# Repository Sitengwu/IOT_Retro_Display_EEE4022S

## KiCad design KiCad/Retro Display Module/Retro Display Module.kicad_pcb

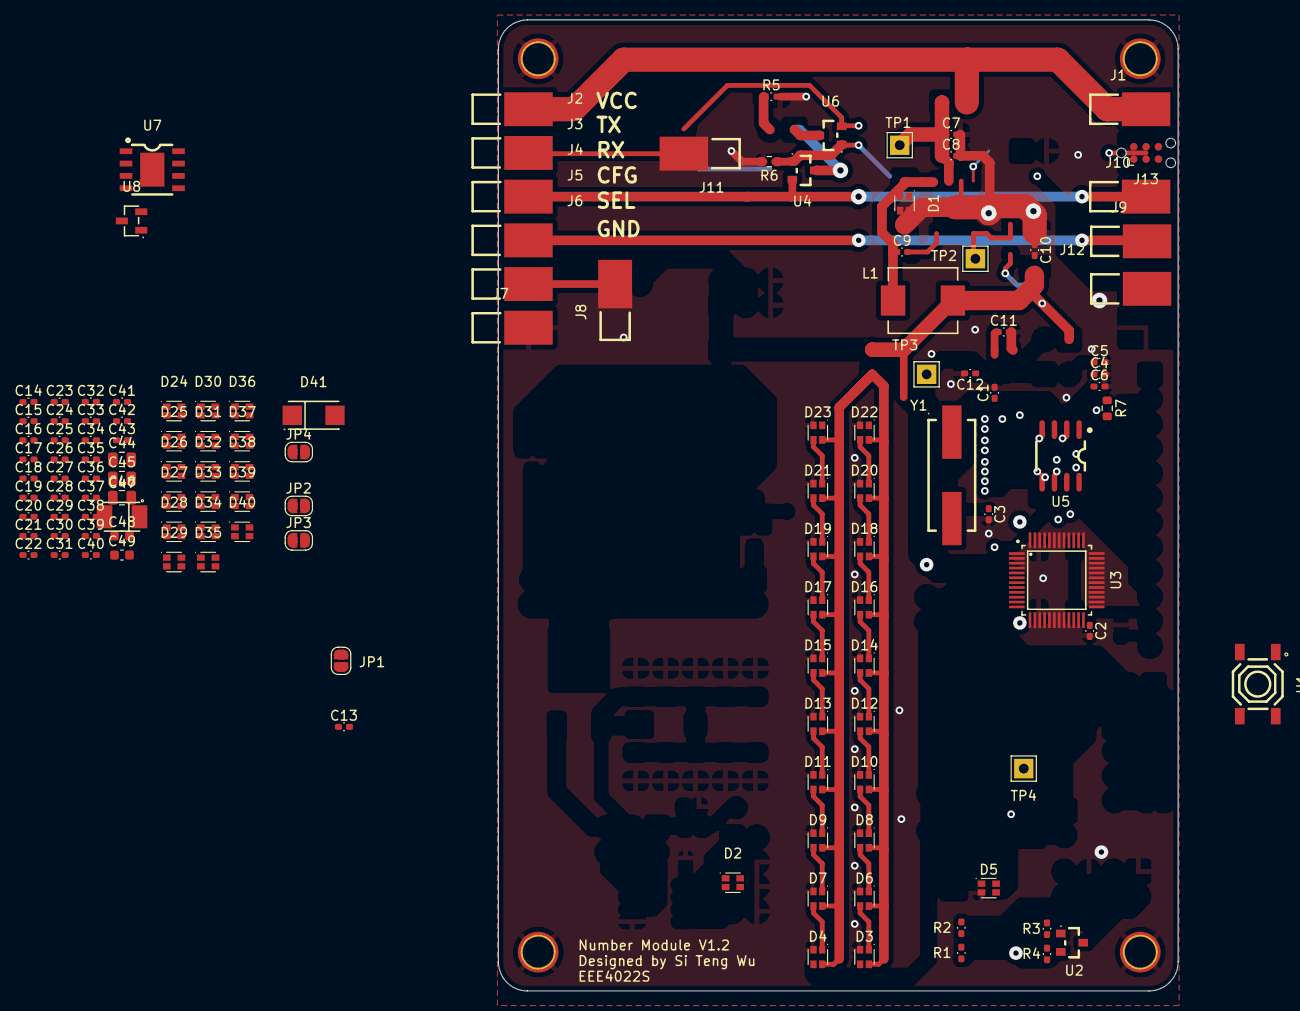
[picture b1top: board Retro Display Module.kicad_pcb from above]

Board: 2 copper layers, 70.0 x 100.0 mm, 132 parts (0 on the bottom side), 64 nets.

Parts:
C1, C3: 10pF; C_0402_1005Metric_Pad0.74x0.62mm_HandSolder
C2, C4, C5, C7, C8, C9, C10, C11, C12, C13, C14, C15, C16, C17, C18, C19, C20, C21, C22, C23, C24, C25, C26, C27, C28, C29, C30, C31, C32, C33, C34, C35, C36, C37, C38, C39, C40, C41, C42, C43: 0.1uF; C_0402_1005Metric_Pad0.74x0.62mm_HandSolder
C6: 4.7uF; C_0402_1005Metric_Pad0.74x0.62mm_HandSolder
C44, C45: 4.7uF; C_0805_2012Metric
C46: 10nF; C_0805_2012Metric
C47: 220uF; CAP-SMD_L3.5-W2.8
C48, C49: 1uF; C_0603_1608Metric
D1, D2, D3, D4, D5, D6, D7, D8, D9, D10, D11, D12, D13, D14, D15, D16, D17, D18, D19, D20, D21, D22, D23, D24, D25, D26, D27, D28, D29, D30, D31, D32, D33, D34, D35, D36, D37, D38, D39, D40: XL-1615RGBC-WS2812B; LED-SMD_4P-L1.6-W1.5_XL-1615RGBC-WS2812B
D41: SS34; SMA_L4.3-W2.6-LS5.2-RD
H1, H2, H3, H4: M3; MountingHole_3.2mm_M3_Pad_TopBottom
J1, J7: VCC; CONN-SMD_YZF0002-38080-02
J2, J8: TX; CONN-SMD_YZF0002-38080-02
J3, J9: RX; CONN-SMD_YZF0002-38080-02
J4, J10: CFG; CONN-SMD_YZF0002-38080-02
J5, J11: SEL; CONN-SMD_YZF0002-38080-02
J6, J12: GND; CONN-SMD_YZF0002-38080-02
J13: Conn_02x03_Odd_Even; Tag-Connect_TC2030-IDC-NL_2x03_P1.27mm_Vertical
JP1, JP2, JP3, JP4: Jumper_2_Open; SolderJumper-2_P1.3mm_Open_RoundedPad1.0x1.5mm
L1: 22uH; IND-SMD_L7.3-W6.6_MHCI06030
R1: 100k; R_0402_1005Metric_Pad0.72x0.64mm_HandSolder
R2, R3, R5: 1k; R_0402_1005Metric_Pad0.72x0.64mm_HandSolder
R4: 10k; R_0402_1005Metric_Pad0.72x0.64mm_HandSolder
R6: 12k; R_0603_1608Metric
R7: 3.9k; R_0603_1608Metric
TP1, TP2, TP3, TP4: TestPoint; TestPoint_THTPad_2.0x2.0mm_Drill1.0mm
U1: TS-1187A-B-A-B; SW-SMD_4P-L5.1-W5.1-P3.70-LS6.5-TL-2
U2, U4, U6: AO3401A; SOT-23_L2.9-W1.3-P1.90-LS2.4-BR
U3: STM32G030C8T6; LQFP-48_L7.0-W7.0-P0.50-LS9.0-BL_1
U5: LM358; Dual LM358
U7: TPS5430DDAR; ESOP-8_L4.9-W3.9-P1.27-LS6.0-TL-EP
U8: XC6206P332MR; SOT-23-3_L2.9-W1.3-P1.90-LS2.4-BR
Y1: Crystal; CRYSTAL-SMD_L11.5-W4.8-LS12.7

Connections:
/3V3: C4.1, C6.1, C7.1, J5.1, J13.1, JP2.1 (A), U3.4 (VBAT), U3.5 (VREF+), U3.6 (VDDA/DDA)
/5V: C8.1, C9.1, C10.1, C11.1, C12.1, C13.1, C14.1, C15.1, C16.1, C17.1, C18.1, C19.1, C20.1, C21.1, C22.1, C23.1, C24.1, C25.1, C26.1, C27.1, C28.1, C29.1, C30.1, C31.1, C32.1, C33.1, C34.1, C35.1, C36.1, C37.1, C38.1, C39.1, C40.1, C41.1, C42.1, C43.1, D1.2 (VDD), D2.2 (VDD), D3.2 (VDD), D4.2 (VDD), D5.2 (VDD), D6.2 (VDD), D7.2 (VDD), D8.2 (VDD), D9.2 (VDD), D10.2 (VDD), D11.2 (VDD), D12.2 (VDD), D13.2 (VDD), D14.2 (VDD), D15.2 (VDD), D16.2 (VDD), D17.2 (VDD), D18.2 (VDD), D19.2 (VDD), D20.2 (VDD), D21.2 (VDD), D22.2 (VDD), D23.2 (VDD), D24.2 (VDD), D25.2 (VDD), D26.2 (VDD), D27.2 (VDD), D28.2 (VDD), D29.2 (VDD), D30.2 (VDD), D31.2 (VDD), D32.2 (VDD), D33.2 (VDD), D34.2 (VDD), D35.2 (VDD), D36.2 (VDD), D37.2 (VDD), D38.2 (VDD), D39.2 (VDD), D40.2 (VDD), JP1.1 (A)
/NRST: C2.1, J13.3, U1.1 (A), U1.2 (B), U3.10 (NRST)
/PA1: J4.1, J10.1, R5.1
/Power/3V3: C49.1, JP2.2 (B), TP4.1, U8.2 (Vout)
/Power/5V: C47.1, C48.1, JP1.2 (B), L1.2, R6.1, TP3.1, U8.3 (Vin)
/Power/VCC: JP3.2 (B), U5.2 (-), U6.3 (D)
/SWDCLK/BOOT: J13.4, R4.2, U3.36 (PA14-BOOT0)
/SWDIO: J13.2, U3.35 (PA13)
/TIM1_CH1: D1.4 (DI), D2.4 (DI), D3.4 (DI), D4.4 (DI), U3.28 (PA8)
/USART2_Rx: J2.1, R2.1
/USART2_Tx: J8.1, R3.1, U4.2 (S)
/VCC: J1.1, J7.1, JP3.1 (A)
GND: C1.2, C2.2, C3.2, C4.2, C5.2, C6.2, C7.2, C8.2, C9.2, C10.2, C11.2, C12.2, C13.2, C14.2, C15.2, C16.2, C17.2, C18.2, C19.2, C20.2, C21.2, C22.2, C23.2, C24.2, C25.2, C26.2, C27.2, C28.2, C29.2, C30.2, C31.2, C32.2, C33.2, C34.2, C35.2, C36.2, C37.2, C38.2, C39.2, C40.2, C41.2, C42.2, C43.2, C44.2, C45.2, C47.2, C48.2, C49.2, D1.3 (GND), D2.3 (GND), D3.3 (GND), D4.3 (GND), D5.3 (GND), D6.3 (GND), D7.3 (GND), D8.3 (GND), D9.3 (GND), D10.3 (GND), D11.3 (GND), D12.3 (GND), D13.3 (GND), D14.3 (GND), D15.3 (GND), D16.3 (GND), D17.3 (GND), D18.3 (GND), D19.3 (GND), D20.3 (GND), D21.3 (GND), D22.3 (GND), D23.3 (GND), D24.3 (GND), D25.3 (GND), D26.3 (GND), D27.3 (GND), D28.3 (GND), D29.3 (GND), D30.3 (GND), D31.3 (GND), D32.3 (GND), D33.3 (GND), D34.3 (GND), D35.3 (GND), D36.3 (GND), D37.3 (GND), D38.3 (GND), D39.3 (GND), D40.3 (GND), D41.2 (A), H1.1, H2.1, H3.1, H4.1, J6.1, J12.1, J13.5, JP4.1 (A), R1.2, R4.1, R7.2, U1.3 (C), U1.4 (D), U3.7 (VSSA/SSA), U5.4 (V-), U5.5 (+), U5.6 (-), U7.6 (GND), U7.9 (PowerPAD), U8.1 (GND)
unnamed: D1.1 (DO), D5.4 (DI)
unnamed: D2.1 (DO), D6.4 (DI)
unnamed: D3.1 (DO), D7.4 (DI)
unnamed: D4.1 (DO), D8.4 (DI)
unnamed: D5.1 (DO), D9.4 (DI)
unnamed: D6.1 (DO), D10.4 (DI)
unnamed: D10.1 (DO), D14.4 (DI)
unnamed: D7.1 (DO), D11.4 (DI)
unnamed: D11.1 (DO), D15.4 (DI)
unnamed: D8.1 (DO), D12.4 (DI)
unnamed: D12.1 (DO), D16.4 (DI)
unnamed: D9.1 (DO), D13.4 (DI)
unnamed: D13.1 (DO), D17.4 (DI)
unnamed: D14.1 (DO), D18.4 (DI)
unnamed: D15.1 (DO), D19.4 (DI)
unnamed: D16.1 (DO), D20.4 (DI)
unnamed: D17.1 (DO), D21.4 (DI)
unnamed: D18.1 (DO), D22.4 (DI)
unnamed: D19.1 (DO), D23.4 (DI)
unnamed: D20.1 (DO), D24.4 (DI)
unnamed: D21.1 (DO), D25.4 (DI)
unnamed: D22.1 (DO), D26.4 (DI)
unnamed: D23.1 (DO), D27.4 (DI)
unnamed: D24.1 (DO), D28.4 (DI)
unnamed: D25.1 (DO), D29.4 (DI)
unnamed: D26.1 (DO), D30.4 (DI)
unnamed: D27.1 (DO), D31.4 (DI)
unnamed: D28.1 (DO), D32.4 (DI)
unnamed: D29.1 (DO), D33.4 (DI)
unnamed: D30.1 (DO), D34.4 (DI)
unnamed: D31.1 (DO), D35.4 (DI)
unnamed: D32.1 (DO), D36.4 (DI)
unnamed: D33.1 (DO), D37.4 (DI)
unnamed: D34.1 (DO), D38.4 (DI)
unnamed: D35.1 (DO), D39.4 (DI)
unnamed: D36.1 (DO), D40.4 (DI)
unnamed: C46.1, D41.1 (K), L1.1, U7.8 (PH)
unnamed: J3.1, J9.1, U2.2 (S)
unnamed: C5.1, J11.1, R1.1, U2.1 (G), U4.1 (G)
unnamed: JP4.2 (B), U7.5 (ENA)
unnamed: U2.3 (D), U4.3 (D)
unnamed: R5.2, U3.12 (PA1)
unnamed: R3.2, U3.13 (PA2)
unnamed: R2.2, U3.14 (PA3)
unnamed: C1.1, U3.8 (PF0-OSC_IN), Y1.1
unnamed: C3.1, U3.9 (PF1-OSC_OUT), Y1.2
unnamed: C44.1, C45.1, TP1.1, U5.3 (+), U5.8 (V+), U6.2 (S), U7.7 (VIN)
unnamed: U5.1, U6.1 (G)
unnamed: C46.2, U7.1 (BOOT)
unnamed: R6.2, R7.1, TP2.1, U7.4 (VSENSE)

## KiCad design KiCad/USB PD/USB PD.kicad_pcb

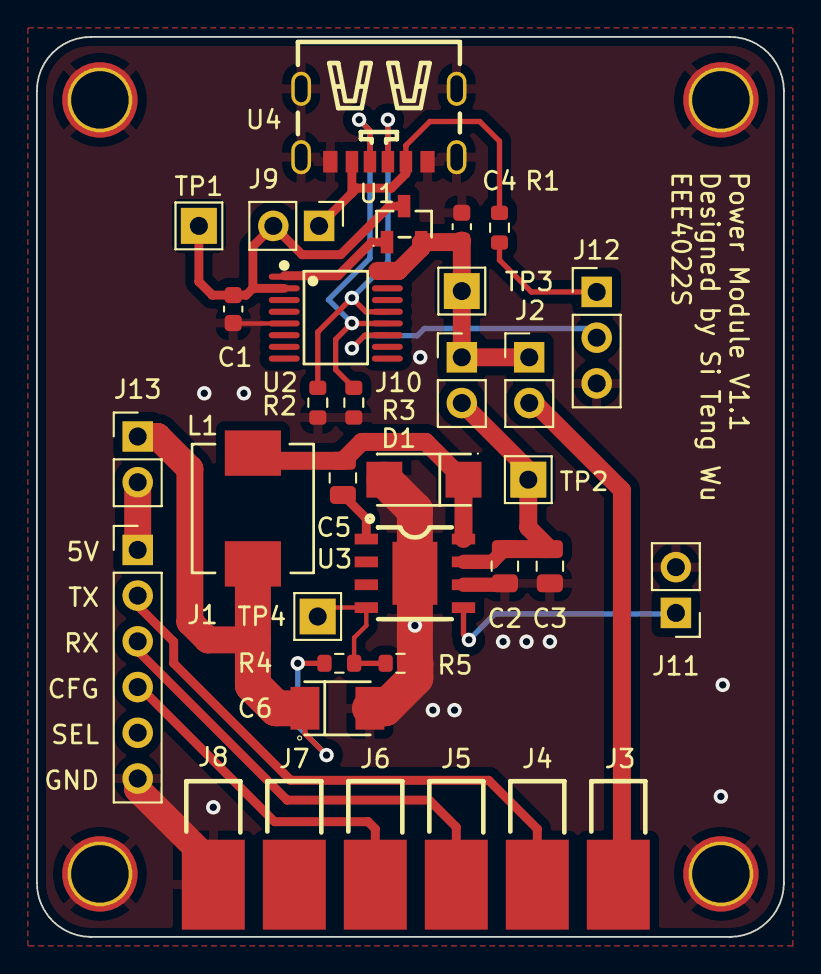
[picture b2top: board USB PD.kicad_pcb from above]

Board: 2 copper layers, 41.5 x 50.0 mm, 38 parts (0 on the bottom side), 20 nets.

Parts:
C1: 1uF; C_0603_1608Metric
C2, C3: 4.7uF; C_0805_2012Metric
C4: 10uF; C_0603_1608Metric
C5: 10nF; C_0805_2012Metric
C6: 220uF; CAP-SMD_L3.5-W2.8
D1: SS34; SMA_L4.3-W2.6-LS5.2-RD
H1, H2, H3, H4: M3; MountingHole_3.2mm_M3_Pad_TopBottom
J1: ESP32 Jumpers; PinHeader_1x06_P2.54mm_Vertical
J2, J9, J10, J11, J13: Conn_01x02_Pin; PinHeader_1x02_P2.54mm_Vertical
J3: VCC; CONN-SMD_YZF0002-38080-02
J4: TX; CONN-SMD_YZF0002-38080-02
J5: RX; CONN-SMD_YZF0002-38080-02
J6: CFG; CONN-SMD_YZF0002-38080-02
J7: SEL; CONN-SMD_YZF0002-38080-02
J8: GND; CONN-SMD_YZF0002-38080-02
J12: Conn_01x03_Pin; PinHeader_1x03_P2.54mm_Vertical
L1: 22uH; IND-SMD_L7.3-W6.6_MHCI06030
R1: 100k; R_0603_1608Metric
R2, R3: 5.1k; R_0603_1608Metric
R4: 12k; R_0603_1608Metric
R5: 3.9k; R_0603_1608Metric
TP1, TP2, TP3, TP4: TestPoint; TestPoint_THTPad_2.0x2.0mm_Drill1.0mm
U1: AO3400A; SOT-23-3_L2.9-W1.3-P1.90-LS2.4-BR
U2: IP2721; TSSOP-16_L5.0-W4.4-P0.65-LS6.4-BL
U3: TPS5430DDAR; ESOP-8_L4.9-W3.9-P1.27-LS6.0-TL-EP
U4: TYPE-C_6P; TYPE-C-SMD_TYPE-C-6P

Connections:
/5V OUT: J1.1, J13.2
/USB_C_VIN: J9.1, R1.1, U4.A9 (VBUS), U4.B9 (VBUS)
/USB_C_VOUT: C4.1, J2.1, J10.1, TP3.1, U1.2 (S), U2.16 (VBUS)
GND: C1.2, C2.2, C3.2, C4.2, C6.2, D1.2 (A), H1.1, H2.1, H3.1, H4.1, J1.6, J8.1, J11.2, J12.3, R2.2, R3.2, R5.2, U2.5 (GND), U3.6 (GND), U3.9 (PowerPAD), U4.7 (EH), U4.A12 (GND), U4.B12 (GND)
unnamed: C5.1, D1.1 (K), L1.1, U3.8 (PH)
unnamed: J1.2, J4.1
unnamed: J1.3, J5.1
unnamed: J1.4, J6.1
unnamed: J2.2, J3.1
unnamed: C1.1, J9.2, TP1.1, U1.3 (D), U2.2 (VIN)
unnamed: C2.1, C3.1, J10.2, TP2.1, U3.7 (VIN)
unnamed: J11.1, U3.5 (ENA)
unnamed: J12.1, R1.2
unnamed: J12.2, U2.11 (SEL)
unnamed: C6.1, J13.1, L1.2, R4.1
unnamed: U1.1 (G), U2.1 (VBUSG)
unnamed: R2.1, U2.13 (CC1), U4.A5 (CC1)
unnamed: R3.1, U2.12 (CC2), U4.B5 (CC2)
unnamed: C5.2, U3.1 (BOOT)
unnamed: R4.2, R5.1, TP4.1, U3.4 (VSENSE)

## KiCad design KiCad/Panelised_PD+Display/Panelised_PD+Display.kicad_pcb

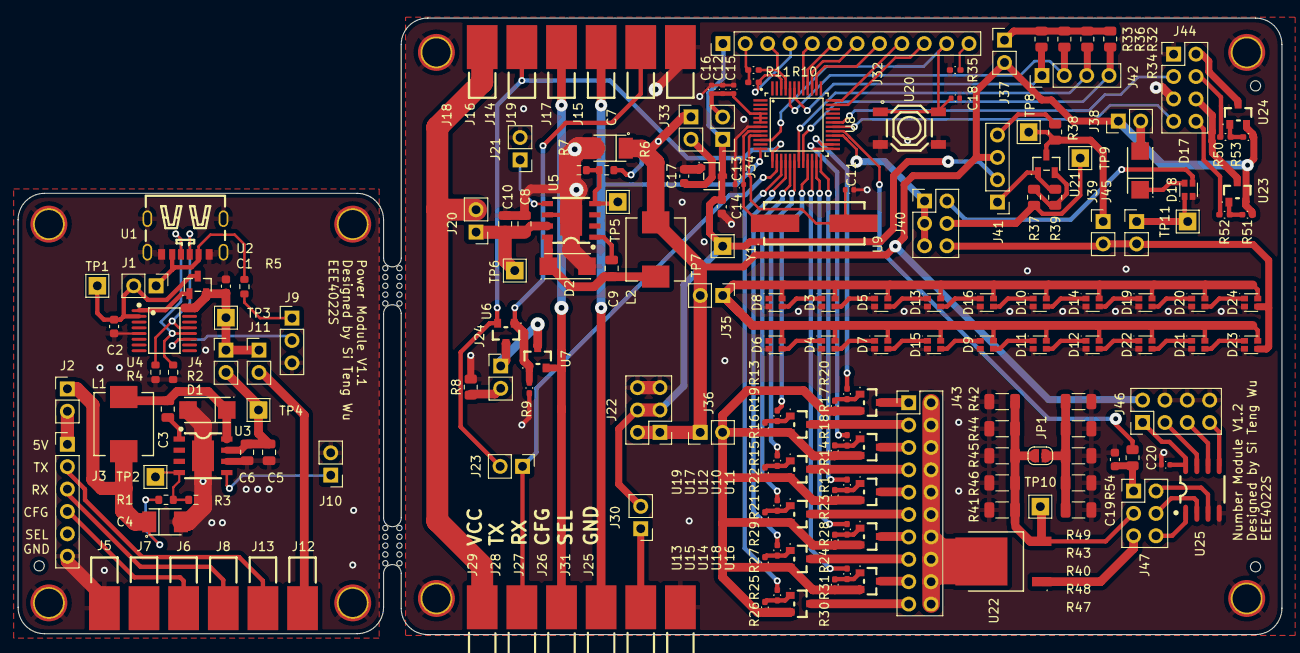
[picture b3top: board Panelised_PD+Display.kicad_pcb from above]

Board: 2 copper layers, 143.5 x 70.0 mm, 195 parts (0 on the bottom side), 133 nets.

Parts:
C1: 10uF; C_0603_1608Metric
C2, C14, C17, C19: 1uF; C_0603_1608Metric
C3, C9: 10nF; C_0805_2012Metric
C4, C7: 220uF; CAP-SMD_L3.5-W2.8
C5, C6, C8, C10: 4.7uF; C_0805_2012Metric
C11, C13: 10pF; C_0402_1005Metric
C12, C15, C18, C20: 0.1uF; C_0402_1005Metric
C16: 4.7uF; C_0402_1005Metric
D1, D2: SS34; SMA_L4.3-W2.6-LS5.2-RD
D3, D4, D5, D6, D7, D8, D9, D10, D11, D12, D13, D14, D15, D16, D18, D19, D20, D21, D22, D23, D24: XL-1615RGBC-WS2812B; LED-SMD_4P-L1.6-W1.5_XL-1615RGBC-WS2812B
D17: M7; SMA_L4.3-W2.6-LS5.2-RD
H1, H2, H3, H4, H5, H6, H7, H8: M3; MountingHole_3.2mm_M3_Pad_TopBottom
J1, J2, J4, J10, J11, J20, J21, J23, J24, J30, J33, J34, J35, J36, J37, J38, J39, J45: Conn_01x02_Pin; PinHeader_1x02_P2.54mm_Vertical
J3: ESP32 Jumpers; PinHeader_1x06_P2.54mm_Vertical
J5, J15, J25: GND; CONN-SMD_YZF0002-38080-02
J6, J19, J26: CFG; CONN-SMD_YZF0002-38080-02
J7, J17, J31: SEL; CONN-SMD_YZF0002-38080-02
J8, J14, J27: RX; CONN-SMD_YZF0002-38080-02
J9: Conn_01x03_Pin; PinHeader_1x03_P2.54mm_Vertical
J12, J18, J29: VCC; CONN-SMD_YZF0002-38080-02
J13, J16, J28: TX; CONN-SMD_YZF0002-38080-02
J22, J40, J47: Conn_02x03_Odd_Even; PinHeader_2x03_P2.54mm_Vertical
J32: Conn_01x12_Pin; PinHeader_1x12_P2.54mm_Vertical
J41, J42: Conn_01x04_Pin; PinHeader_1x04_P2.54mm_Vertical
J43: Conn_02x11_Odd_Even; PinHeader_2x10_P2.54mm_Vertical
J44, J46: Conn_02x04_Odd_Even; PinHeader_2x04_P2.54mm_Vertical
JP1: Jumper_2_Open; SolderJumper-2_P1.3mm_Open_RoundedPad1.0x1.5mm
L1, L2: 22uH; IND-SMD_L7.3-W6.6_MHCI06030
R1, R6: 12k; R_0603_1608Metric
R2, R4: 5.1k; R_0603_1608Metric
R3, R7: 3.9k; R_0603_1608Metric
R5: 100k; R_0603_1608Metric
R8, R37, R38, R39: 1k; R_0805_2012Metric
R9, R14, R15, R17, R19, R21, R23, R24, R26, R27, R30, R51, R53: 100k; R_0402_1005Metric_Pad0.72x0.64mm_HandSolder
R10, R11, R35: 10k; R_0402_1005Metric_Pad0.72x0.64mm_HandSolder
R12, R13, R16, R18, R20, R22, R25, R28, R29, R31, R50, R52: 1k; R_0402_1005Metric_Pad0.72x0.64mm_HandSolder
R32, R33, R34, R36: 4.7k; R_0805_2012Metric
R40, R41, R42, R43, R44, R45, R46, R47, R48, R49: 100; R_1206_3216Metric
R54: 10k; R_0805_2012Metric
TP1, TP2, TP3, TP4, TP5, TP6, TP7, TP8, TP9, TP10, TP11: TestPoint; TestPoint_THTPad_2.0x2.0mm_Drill1.0mm
U1: TYPE-C_6P; TYPE-C-SMD_TYPE-C-6P
U2: AO3400A; SOT-23-3_L2.9-W1.3-P1.90-LS2.4-BR
U3, U5: TPS5430DDAR; ESOP-8_L4.9-W3.9-P1.27-LS6.0-TL-EP
U4: IP2721; TSSOP-16_L5.0-W4.4-P0.65-LS6.4-BL
U6, U7, U10, U11, U12, U13, U14, U15, U16, U17, U18, U19, U23, U24: AO3401A; SOT-23_L2.9-W1.3-P1.90-LS2.4-BR
U8: STM32G030C8T6; LQFP-48_L7.0-W7.0-P0.50-LS9.0-BL_1
U9: XC6206P332MR; XC6206
U20: TS-1187A-B-A-B; SW-SMD_4P-L5.1-W5.1-P3.70-LS6.5-TL-2
U21: 2N7002; SOT-23-3_L2.9-W1.3-P1.90-LS2.4-BR
U22: MJD44H11J; MJD44 NPN
U25: LM358DR2G; Dual LM358
Y1: Crystal; CRYSTAL-SMD_L11.5-W4.8-LS12.7
mouse-bite-1, mouse-bite-2: VAL**; mouse-bite-2mm-slot

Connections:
/3V3: C14.1, J22.3, J22.4, J30.2, J32.1, J34.1, J41.2, TP7.1, U9.3 (Vout)
/5V: C7.1, J22.1, J22.2, J33.1, J35.2, J36.1, J37.2, J38.1, J41.3, J46.2, L2.2, R6.1, R51.1, R53.1, U23.2 (S), U24.2 (S)
/5V OUT: J2.2, J3.1
/I2C1_SCL: J32.3, R10.2, U8.45 (PB6)
/I2C1_SDA: J32.4, R11.2, U8.46 (PB7)
/I2C_PUR: J32.2, R10.1, R11.1
/LED Driver/1OUT: J47.5, U22.1 (B)
/LED Driver/5V_PWR: J36.2, R14.1, R15.1, R17.1, R19.1, R21.1, R23.1, R24.1, R26.1, R27.1, R30.1, U10.2 (S), U11.2 (S), U12.2 (S), U13.2 (S), U14.2 (S), U15.2 (S), U16.2 (S), U17.2 (S), U18.2 (S), U19.2 (S)
/LED Driver/-ve: J47.3, JP1.1 (A), R41.1, R42.1, R44.1, R45.1, R46.1, TP10.1, U22.3 (E)
/LED Driver/LED0: J43.1, U11.3 (D)
/LED Driver/LED1: J43.19, U16.3 (D)
/LED Driver/LED2: J43.17, U19.3 (D)
/LED Driver/LED3: J43.15, U18.3 (D)
/LED Driver/LED4: J43.13, U17.3 (D)
/LED Driver/LED5: J43.11, U14.3 (D)
/LED Driver/LED6: J43.9, U12.3 (D)
/LED Driver/LED7: J43.7, U15.3 (D)
/LED Driver/LED8: J43.5, U10.3 (D)
/LED Driver/LED9: J43.3, U13.3 (D)
/LED Driver/main_col: J43.2, J43.4, J43.6, J43.8, J43.10, J43.12, J43.14, J43.16, J43.18, J43.20, U22.2 (C)
/NRST: C18.1, J32.11, U8.10 (NRST), U20.1 (A), U20.2 (B)
/PA1: J19.1, J26.1, U8.12 (PA1)
/PA4: R25.2, U8.15 (PA4)
/PA5: R29.2, U8.16 (PA5)
/PA6: R22.2, U8.17 (PA6)
/PA7: R16.2, U8.18 (PA7)
/PB2: R13.2, U8.21 (PB2)
/PB10: R31.2, U8.22 (PB10)
/PB11: R28.2, U8.23 (PB11)
/PB12: R12.2, U8.24 (PB12)
/PB13: R18.2, U8.25 (PB13)
/PB14: R20.2, U8.26 (PB14)
/PC6: J44.8, R52.2
/PC7: J44.4, R50.2
/PD1: J32.7, U8.39 (PD1)
/PD2: J32.6, U8.40 (PD2)
/PD3: J32.5, U8.41 (PD3)
/PDO: J32.8, U8.38 (PD0)
/RGB LEDs/Cheese: D18.4 (DI), J40.2
/RGB LEDs/DIN: D23.4 (DI), D24.4 (DI), J39.2, J40.6, J45.2
/RGB LEDs/Level: J40.4, R39.2, TP9.1
/SWDCLK/BOOT: J32.9, U8.36 (PA14-BOOT0)
/SWDIO: J32.10, U8.35 (PA13)
/TIM1_CH1: J40.1, J40.3, J40.5, U8.28 (PA8)
/TIM1_CH2: R54.2, U8.29 (PA9)
/TIM3_CH1: J42.1, R33.2, U8.43 (PB4)
/TIM3_CH2: J42.2, R36.2, U8.44 (PB5)
/TIM3_CH3: J42.3, R32.2, U8.19 (PB0)
/TIM3_CH4: J42.4, R34.2, U8.20 (PB1)
/USART2_Rx: J23.1, J28.1, U8.14 (PA3)
/USART2_Tx: J16.1, J23.2, U6.2 (S), U8.13 (PA2)
/USB_C_VIN: J1.1, R5.1, U1.A9 (VBUS), U1.B9 (VBUS)
/USB_C_VOUT: C1.1, J4.1, J11.1, TP3.1, U2.2 (S), U4.16 (VBUS)
/VCC: J18.1, J20.2, J29.1
/VR/B: C12.1, C15.1, C16.1, J34.2, U8.4 (VBAT), U8.5 (VREF+), U8.6 (VDDA/DDA)
GND: C1.2, C2.2, C4.2, C5.2, C6.2, C7.2, C8.2, C10.2, C11.2, C12.2, C13.2, C14.2, C15.2, C16.2, C17.2, C18.2, C19.2, C20.2, D1.2 (A), D2.2 (A), D3.3 (GND), D4.3 (GND), D5.3 (GND), D6.3 (GND), D7.3 (GND), D8.3 (GND), D9.3 (GND), D10.3 (GND), D11.3 (GND), D12.3 (GND), D13.3 (GND), D14.3 (GND), D15.3 (GND), D16.3 (GND), D18.3 (GND), D19.3 (GND), D20.3 (GND), D21.3 (GND), D22.3 (GND), D23.3 (GND), D24.3 (GND), H1.1, H2.1, H3.1, H4.1, H5.1, H6.1, H7.1, H8.1, J3.6, J5.1, J9.3, J10.2, J15.1, J21.2, J22.5, J22.6, J25.1, J44.1, J44.5, J46.4, J46.6, J46.8, R2.2, R3.2, R4.2, R7.2, R8.2, R35.1, R40.2, R41.2, R42.2, R43.2, R44.2, R45.2, R46.2, R47.2, R48.2, R49.2, U1.7 (EH), U1.A12 (GND), U1.B12 (GND), U3.6 (GND), U3.9 (PowerPAD), U4.5 (GND), U5.6 (GND), U5.9 (PowerPAD), U8.7 (VSSA/SSA), U9.1 (GND), U20.3 (C), U20.4 (D), U25.4 (GND)
unnamed: C3.1, C9.1, D1.1 (K), D2.1 (K), L1.1, L2.1, U3.8 (PH), U5.8 (PH)
unnamed: D17.2 (A), J38.2
unnamed: D17.1 (K), D18.2 (VDD)
unnamed: D20.4 (DI), D24.1 (DO)
unnamed: D21.4 (DI), D23.1 (DO)
unnamed: D18.1 (DO), J45.1, TP11.1
unnamed: D19.4 (DI), D20.1 (DO)
unnamed: D21.1 (DO), D22.4 (DI)
unnamed: D14.4 (DI), D19.1 (DO)
unnamed: D10.4 (DI), D14.1 (DO)
unnamed: D3.2 (VDD), D4.2 (VDD), D5.2 (VDD), D6.2 (VDD), D7.2 (VDD), D8.2 (VDD), D9.2 (VDD), D10.2 (VDD), D11.2 (VDD), D12.2 (VDD), D13.2 (VDD), D14.2 (VDD), D15.2 (VDD), D16.2 (VDD), D19.2 (VDD), D20.2 (VDD), D21.2 (VDD), D22.2 (VDD), D23.2 (VDD), D24.2 (VDD), J35.1
unnamed: D12.4 (DI), D22.1 (DO)
unnamed: D11.4 (DI), D12.1 (DO)
unnamed: D10.1 (DO), D16.4 (DI)
unnamed: D9.4 (DI), D11.1 (DO)
unnamed: D13.4 (DI), D16.1 (DO)
unnamed: D9.1 (DO), D15.4 (DI)
unnamed: D5.4 (DI), D13.1 (DO)
unnamed: D7.4 (DI), D15.1 (DO)
unnamed: D3.4 (DI), D5.1 (DO)
unnamed: D4.4 (DI), D7.1 (DO)
unnamed: D3.1 (DO), D8.4 (DI)
unnamed: D4.1 (DO), D6.4 (DI)
unnamed: J3.2, J13.1, J44.2, U24.3 (D)
unnamed: J3.3, J8.1, J44.3, U8.31 (PC7)
unnamed: J3.4, J6.1
unnamed: J44.6, U23.3 (D)
unnamed: J44.7, U8.30 (PC6)
unnamed: J11.2, J12.1
unnamed: J30.1, J31.1
unnamed: C2.1, J1.2, TP1.1, U2.3 (D), U4.2 (VIN)
unnamed: J24.1, U6.3 (D), U7.3 (D)
unnamed: C5.1, C6.1, J4.2, J24.2, R8.1, TP4.1, U3.7 (VIN)
unnamed: J10.1, U3.5 (ENA)
unnamed: J9.1, R5.2
unnamed: J9.2, U4.11 (SEL)
unnamed: C4.1, J2.1, L1.2, R1.1
unnamed: J14.1, J27.1, U7.2 (S)
unnamed: J17.1, U6.1 (G), U7.1 (G)
unnamed: J32.12, R35.2
unnamed: J37.1, R32.1, R33.1, R34.1, R36.1
unnamed: C8.1, C10.1, J20.1, TP6.1, U5.7 (VIN)
unnamed: J21.1, U5.5 (ENA)
unnamed: C17.1, J33.2, U9.2 (Vin)
unnamed: J41.1, R37.2, U21.1 (G)
unnamed: J41.4, R38.2
unnamed: J39.1, R38.1, TP8.1, U21.3 (D)
unnamed: C19.1, J47.1, R54.1
unnamed: J47.2, U25.3 (1IN+)
unnamed: J47.4, U25.2 (1IN-)
unnamed: J47.6, U25.1 (1OUT)
unnamed: C20.1, J46.1, U25.8 (VCC)
unnamed: J46.3, U25.7 (2OUT)
unnamed: J46.5, U25.6 (2IN-)
unnamed: J46.7, U25.5 (2IN+)
unnamed: JP1.2 (B), R40.1, R43.1, R47.1, R48.1, R49.1
unnamed: R51.2, R52.1, U2.1 (G), U4.1 (VBUSG), U23.1 (G)
unnamed: R4.1, U1.A5 (CC1), U4.13 (CC1)
unnamed: R2.1, U1.B5 (CC2), U4.12 (CC2)
unnamed: R50.1, R53.2, U24.1 (G)
unnamed: C3.2, U3.1 (BOOT)
unnamed: R1.2, R3.1, TP2.1, U3.4 (VSENSE)
unnamed: C13.1, U8.8 (PF0-OSC_IN), Y1.1
unnamed: C11.1, U8.9 (PF1-OSC_OUT), Y1.2
unnamed: C9.2, U5.1 (BOOT)
unnamed: R6.2, R7.1, TP5.1, U5.4 (VSENSE)
unnamed: R37.1, R39.1, U21.2 (S)
unnamed: R25.1, R26.2, U16.1 (G)
unnamed: R12.1, R23.2, U12.1 (G)
unnamed: R30.2, R31.1, U19.1 (G)
unnamed: R15.2, R16.1, U15.1 (G)
unnamed: R27.2, R29.1, U18.1 (G)
unnamed: R14.2, R18.1, U10.1 (G)
unnamed: R24.2, R28.1, U17.1 (G)
unnamed: R13.1, R19.2, U13.1 (G)
unnamed: R21.2, R22.1, U14.1 (G)
unnamed: R17.2, R20.1, U11.1 (G)

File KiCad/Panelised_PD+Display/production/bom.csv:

Designator,Footprint,Quantity,Value,LCSC Part #
C1,0603,1,10uF,C19702
"C10, C5, C6, C8",0805,4,4.7uF,C1779
"C11, C13",0402,2,10pF,C32949
"C12, C15, C18, C20",0402,4,0.1uF,C1525
"C14, C17, C19, C2",0603,4,1uF,C15849
C16,0402,1,4.7uF,C23733
"C3, C9",0805,2,10nF,C1710
"C4, C7",CAP-SMD_L3.5-W2.8,2,220uF,C212682
"D1, D2",SMA_L4.3-W2.6-LS5.2-RD,2,SS34,C8678
"D10, D11, D12, D13, D14, D15, D16, D18, D19, D20, D21, D22, D23, D24, D3, D4, D5, D6, D7, D8, D9",LED-SMD_4P-L1.6-W1.5_XL-1615RGBC-WS2812B,21,XL-1615RGBC-WS2812B,C5349954
D17,SMA_L4.3-W2.6-LS5.2-RD,1,M7,C95872
"J12, J18, J29",CONN-SMD_YZF0002-38080-02,3,VCC,C5203987
"J13, J16, J28",CONN-SMD_YZF0002-38080-02,3,TX,C5203987
"J14, J27, J8",CONN-SMD_YZF0002-38080-02,3,RX,C5203987
"J15, J25, J5",CONN-SMD_YZF0002-38080-02,3,GND,C5203987
"J17, J31, J7",CONN-SMD_YZF0002-38080-02,3,SEL,C5203987
"J19, J26, J6",CONN-SMD_YZF0002-38080-02,3,CFG,C5203987
"L1, L2",IND-SMD_L7.3-W6.6_MHCI06030,2,22uH,C128694
"R1, R6",0603,2,12k,C22790
"R10, R11, R35",0402,3,10k,C25744
"R12, R13, R16, R18, R20, R22, R25, R28, R29, R31, R50, R52",0402,12,1k,C11702
"R14, R15, R17, R19, R21, R23, R24, R26, R27, R30, R51, R53, R9",0402,13,100k,C25741
"R2, R4",0603,2,5.1k,C23186
"R3, R7",0603,2,3.9k,C23018
"R32, R33, R34, R36",0805,4,4.7k,C17673
"R37, R38, R39, R8",0805,4,1k,C17513
"R40, R41, R42, R43, R44, R45, R46, R47, R48, R49",1206,10,100,C17901
R5,0603,1,100k,C25803
R54,0805,1,10k,C17414
U1,TYPE-C-SMD_TYPE-C-6P,1,TYPE-C_6P,C456012
"U10, U11, U12, U13, U14, U15, U16, U17, U18, U19, U23, U24, U6, U7",SOT-23_L2.9-W1.3-P1.90-LS2.4-BR,14,AO3401A,C15127
U2,SOT-23-3_L2.9-W1.3-P1.90-LS2.4-BR,1,AO3400A,C20917
U20,SW-SMD_4P-L5.1-W5.1-P3.70-LS6.5-TL-2,1,TS-1187A-B-A-B,C318884
U21,SOT-23-3_L2.9-W1.3-P1.90-LS2.4-BR,1,2N7002,C8545
U22,MJD44 NPN,1,MJD44H11J,C551528
U25,Dual LM358,1,LM358DR2G,C7950
"U3, U5",ESOP-8_L4.9-W3.9-P1.27-LS6.0-TL-EP,2,TPS5430DDAR,C9864
U4,TSSOP-16_L5.0-W4.4-P0.65-LS6.4-BL,1,IP2721,C603176
U8,LQFP-48_L7.0-W7.0-P0.50-LS9.0-BL_1,1,STM32G030C8T6,C529329
U9,XC6206,1,XC6206P332MR,C5446
Y1,CRYSTAL-SMD_L11.5-W4.8-LS12.7,1,Crystal,C12674

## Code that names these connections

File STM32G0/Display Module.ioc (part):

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Mcu.Name=STM32G030C(6-8)Tx
Mcu.Package=LQFP48
Mcu.UserName=STM32G030C8Tx
PA0.GPIOParameters=GPIO_ModeDefaultEXTI
PA0.GPIO_ModeDefaultEXTI=GPIO_MODE_IT_FALLING
PA0.Signal=GPXTI0
PA13.Mode=Serial_Wire
PA13.Signal=SYS_SWDIO
PA14-BOOT0.Mode=Serial_Wire
PA14-BOOT0.Signal=SYS_SWCLK
PA2.Mode=Asynchronous
PA2.Signal=USART2_TX
PA3.Mode=Asynchronous
PA3.Signal=USART2_RX
PA4.GPIOParameters=GPIO_PuPd,GPIO_Label,GPIO_ModeDefaultOutputPP
PA4.GPIO_Label=LED1
PA4.GPIO_ModeDefaultOutputPP=GPIO_MODE_OUTPUT_OD
PA4.GPIO_PuPd=GPIO_NOPULL
PA4.Signal=GPIO_Output
PA5.GPIOParameters=GPIO_PuPd,GPIO_Label,GPIO_ModeDefaultOutputPP
PA5.GPIO_Label=LED3
PA5.GPIO_ModeDefaultOutputPP=GPIO_MODE_OUTPUT_OD
PA5.GPIO_PuPd=GPIO_NOPULL
PA5.Signal=GPIO_Output
PA6.GPIOParameters=GPIO_PuPd,GPIO_Label,GPIO_ModeDefaultOutputPP
PA6.GPIO_Label=LED5
PA6.GPIO_ModeDefaultOutputPP=GPIO_MODE_OUTPUT_OD
PA6.GPIO_PuPd=GPIO_NOPULL
PA6.Signal=GPIO_Output
PA7.GPIOParameters=GPIO_PuPd,GPIO_Label,GPIO_ModeDefaultOutputPP
PA7.GPIO_Label=LED7
PA7.GPIO_ModeDefaultOutputPP=GPIO_MODE_OUTPUT_OD
PA7.GPIO_PuPd=GPIO_NOPULL
PA7.Signal=GPIO_Output
PA8.Signal=S_TIM1_CH1
PA9.Signal=S_TIM1_CH2
PB10.GPIOParameters=GPIO_PuPd,GPIO_Label,GPIO_ModeDefaultOutputPP
PB10.GPIO_Label=LED2
PB10.GPIO_ModeDefaultOutputPP=GPIO_MODE_OUTPUT_OD
PB10.GPIO_PuPd=GPIO_NOPULL
PB10.Signal=GPIO_Output
PB11.GPIOParameters=GPIO_PuPd,GPIO_Label,GPIO_ModeDefaultOutputPP
PB11.GPIO_Label=LED4
PB11.GPIO_ModeDefaultOutputPP=GPIO_MODE_OUTPUT_OD
PB11.GPIO_PuPd=GPIO_NOPULL
PB11.Signal=GPIO_Output
PB12.GPIOParameters=GPIO_PuPd,GPIO_Label,GPIO_ModeDefaultOutputPP
PB12.GPIO_Label=LED6
PB12.GPIO_ModeDefaultOutputPP=GPIO_MODE_OUTPUT_OD
PB12.GPIO_PuPd=GPIO_NOPULL
PB12.Signal=GPIO_Output
PB13.GPIOParameters=GPIO_PuPd,GPIO_Label,GPIO_ModeDefaultOutputPP
PB13.GPIO_Label=LED8
PB13.GPIO_ModeDefaultOutputPP=GPIO_MODE_OUTPUT_OD
PB13.GPIO_PuPd=GPIO_NOPULL
PB13.Signal=GPIO_Output
PB14.GPIOParameters=GPIO_PuPd,GPIO_Label,GPIO_ModeDefaultOutputPP
PB14.GPIO_Label=LED0
PB14.GPIO_ModeDefaultOutputPP=GPIO_MODE_OUTPUT_OD
PB14.GPIO_PuPd=GPIO_NOPULL
PB14.Signal=GPIO_Output
PB2.GPIOParameters=GPIO_PuPd,GPIO_Label,GPIO_ModeDefaultOutputPP
PB2.GPIO_Label=LED9
PB2.GPIO_ModeDefaultOutputPP=GPIO_MODE_OUTPUT_OD
PB2.GPIO_PuPd=GPIO_NOPULL
PB2.Signal=GPIO_Output
PF0-OSC_IN\ (PF0).Mode=HSE-External-Oscillator
PF0-OSC_IN\ (PF0).Signal=RCC_OSC_IN
PF1-OSC_OUT\ (PF1).Mode=HSE-External-Oscillator
PF1-OSC_OUT\ (PF1).Signal=RCC_OSC_OUT
RCC.HSE_VALUE=8000000
RCC.SYSCLKFreq_VALUE=64000000
RCC.SYSCLKSource=RCC_SYSCLKSOURCE_PLLCLK
board=custom

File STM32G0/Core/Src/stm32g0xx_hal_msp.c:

/* USER CODE BEGIN Header */
/**
  ******************************************************************************
  * @file         stm32g0xx_hal_msp.c
  * @brief        This file provides code for the MSP Initialization
  *               and de-Initialization codes.
  ******************************************************************************
  * @attention
  *
  * Copyright (c) 2024 STMicroelectronics.
  * All rights reserved.
  *
  * This software is licensed under terms that can be found in the LICENSE file
  * in the root directory of this software component.
  * If no LICENSE file comes with this software, it is provided AS-IS.
  *
  ******************************************************************************
  */
/* USER CODE END Header */

/* Includes ------------------------------------------------------------------*/
#include "main.h"
/* USER CODE BEGIN Includes */

/* USER CODE END Includes */

/* Private typedef -----------------------------------------------------------*/
/* USER CODE BEGIN TD */

/* USER CODE END TD */

/* Private define ------------------------------------------------------------*/
/* USER CODE BEGIN Define */

/* USER CODE END Define */

/* Private macro -------------------------------------------------------------*/
/* USER CODE BEGIN Macro */

/* USER CODE END Macro */

/* Private variables ---------------------------------------------------------*/
/* USER CODE BEGIN PV */

/* USER CODE END PV */

/* Private function prototypes -----------------------------------------------*/
/* USER CODE BEGIN PFP */

/* USER CODE END PFP */

/* External functions --------------------------------------------------------*/
/* USER CODE BEGIN ExternalFunctions */

/* USER CODE END ExternalFunctions */

/* USER CODE BEGIN 0 */

/* USER CODE END 0 */

void HAL_TIM_MspPostInit(TIM_HandleTypeDef *htim);
                    /**
  * Initializes the Global MSP.
  */
void HAL_MspInit(void)
{

  /* USER CODE BEGIN MspInit 0 */

  /* USER CODE END MspInit 0 */

  __HAL_RCC_SYSCFG_CLK_ENABLE();
  __HAL_RCC_PWR_CLK_ENABLE();

  /* System interrupt init*/

  /* USER CODE BEGIN MspInit 1 */

  /* USER CODE END MspInit 1 */
}

/**
* @brief TIM_Base MSP Initialization
* This function configures the hardware resources used in this example
* @param htim_base: TIM_Base handle pointer
* @retval None
*/
void HAL_TIM_Base_MspInit(TIM_HandleTypeDef* htim_base)
{
  if(htim_base->Instance==TIM1)
  {
  /* USER CODE BEGIN TIM1_MspInit 0 */

  /* USER CODE END TIM1_MspInit 0 */
    /* Peripheral clock enable */
    __HAL_RCC_TIM1_CLK_ENABLE();
  /* USER CODE BEGIN TIM1_MspInit 1 */

  /* USER CODE END TIM1_MspInit 1 */

  }

}

void HAL_TIM_MspPostInit(TIM_HandleTypeDef* htim)
{
  GPIO_InitTypeDef GPIO_InitStruct = {0};
  if(htim->Instance==TIM1)
  {
  /* USER CODE BEGIN TIM1_MspPostInit 0 */

  /* USER CODE END TIM1_MspPostInit 0 */

    __HAL_RCC_GPIOA_CLK_ENABLE();
    /**TIM1 GPIO Configuration
    PA8     ------> TIM1_CH1
    PA9     ------> TIM1_CH2
    */
    GPIO_InitStruct.Pin = GPIO_PIN_8|GPIO_PIN_9;
    GPIO_InitStruct.Mode = GPIO_MODE_AF_PP;
    GPIO_InitStruct.Pull = GPIO_NOPULL;
    GPIO_InitStruct.Speed = GPIO_SPEED_FREQ_LOW;
    GPIO_InitStruct.Alternate = GPIO_AF2_TIM1;
    HAL_GPIO_Init(GPIOA, &GPIO_InitStruct);

  /* USER CODE BEGIN TIM1_MspPostInit 1 */

  /* USER CODE END TIM1_MspPostInit 1 */
  }

}
/**
* @brief TIM_Base MSP De-Initialization
* This function freeze the hardware resources used in this example
* @param htim_base: TIM_Base handle pointer
* @retval None
*/
void HAL_TIM_Base_MspDeInit(TIM_HandleTypeDef* htim_base)
{
  if(htim_base->Instance==TIM1)
  {
  /* USER CODE BEGIN TIM1_MspDeInit 0 */

  /* USER CODE END TIM1_MspDeInit 0 */
    /* Peripheral clock disable */
    __HAL_RCC_TIM1_CLK_DISABLE();
  /* USER CODE BEGIN TIM1_MspDeInit 1 */

  /* USER CODE END TIM1_MspDeInit 1 */
  }

}

/**
* @brief UART MSP Initialization
* This function configures the hardware resources used in this example
* @param huart: UART handle pointer
* @retval None
*/
void HAL_UART_MspInit(UART_HandleTypeDef* huart)
{
  GPIO_InitTypeDef GPIO_InitStruct = {0};
  if(huart->Instance==USART2)
  {
  /* USER CODE BEGIN USART2_MspInit 0 */

  /* USER CODE END USART2_MspInit 0 */
    /* Peripheral clock enable */
    __HAL_RCC_USART2_CLK_ENABLE();

    __HAL_RCC_GPIOA_CLK_ENABLE();
    /**USART2 GPIO Configuration
    PA2     ------> USART2_TX
    PA3     ------> USART2_RX
    */
    GPIO_InitStruct.Pin = GPIO_PIN_2|GPIO_PIN_3;
    GPIO_InitStruct.Mode = GPIO_MODE_AF_PP;
    GPIO_InitStruct.Pull = GPIO_NOPULL;
    GPIO_InitStruct.Speed = GPIO_SPEED_FREQ_LOW;
    GPIO_InitStruct.Alternate = GPIO_AF1_USART2;
    HAL_GPIO_Init(GPIOA, &GPIO_InitStruct);

    /* USART2 interrupt Init */
    HAL_NVIC_SetPriority(USART2_IRQn, 3, 0);
    HAL_NVIC_EnableIRQ(USART2_IRQn);
  /* USER CODE BEGIN USART2_MspInit 1 */

  /* USER CODE END USART2_MspInit 1 */

  }

}

/**
* @brief UART MSP De-Initialization
* This function freeze the hardware resources used in this example
* @param huart: UART handle pointer
* @retval None
*/
void HAL_UART_MspDeInit(UART_HandleTypeDef* huart)
{
  if(huart->Instance==USART2)
  {
  /* USER CODE BEGIN USART2_MspDeInit 0 */

  /* USER CODE END USART2_MspDeInit 0 */
    /* Peripheral clock disable */
    __HAL_RCC_USART2_CLK_DISABLE();

    /**USART2 GPIO Configuration
    PA2     ------> USART2_TX
    PA3     ------> USART2_RX
    */
    HAL_GPIO_DeInit(GPIOA, GPIO_PIN_2|GPIO_PIN_3);

    /* USART2 interrupt DeInit */
    HAL_NVIC_DisableIRQ(USART2_IRQn);
  /* USER CODE BEGIN USART2_MspDeInit 1 */

  /* USER CODE END USART2_MspDeInit 1 */
  }

}

/* USER CODE BEGIN 1 */

/* USER CODE END 1 */

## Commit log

2024-07-31 Add new Kicad Files
2024-08-07 Added PubSubClient library files
2024-09-09 Add: PCB
2024-09-09 Added Switch 3D Model
2024-09-10 Updated USB PD and Driver LED circuit
2024-09-10 Updated Display Board schematic and Ltspice simulations
2024-09-11 Updated Display PCB
2024-10-01 Begin STM32 Programming
2024-11-08 Final Commit for 4022S
2024-11-08 Small Changes
2024-11-08 Updating Code to add colour changing
2024-11-08 Updated Schematics and Added Reverse polarity protection
2024-12-05 Added reverse polarity protection
